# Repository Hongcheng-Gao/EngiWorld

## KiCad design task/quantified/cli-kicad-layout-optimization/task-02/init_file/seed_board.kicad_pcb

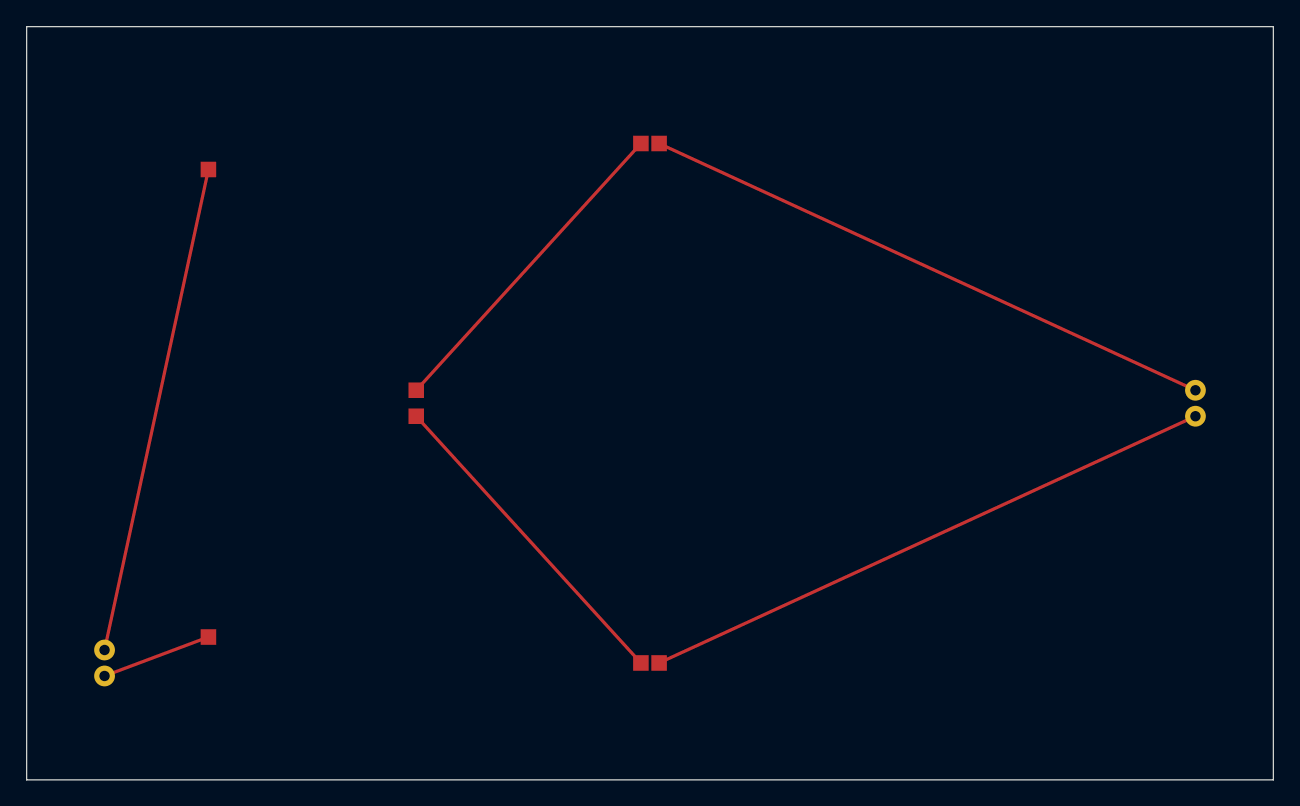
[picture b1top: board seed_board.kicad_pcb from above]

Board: 2 copper layers, 96.0 x 58.0 mm, 7 parts (0 on the bottom side), 6 nets.

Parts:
C1, C2: 100nF
J1: DIFF_CONNECTOR
J2: BYPASS_CONNECTOR
R1, R2: 49.9R
U1: DIFF_DRIVER

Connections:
J2_C1: C1.1, J2.1
J2_C2: C2.1, J2.2
R1_J1: J1.1, R1.2
R2_J1: J1.2, R2.2
U1_R1: R1.1, U1.1
U1_R2: R2.1, U1.2

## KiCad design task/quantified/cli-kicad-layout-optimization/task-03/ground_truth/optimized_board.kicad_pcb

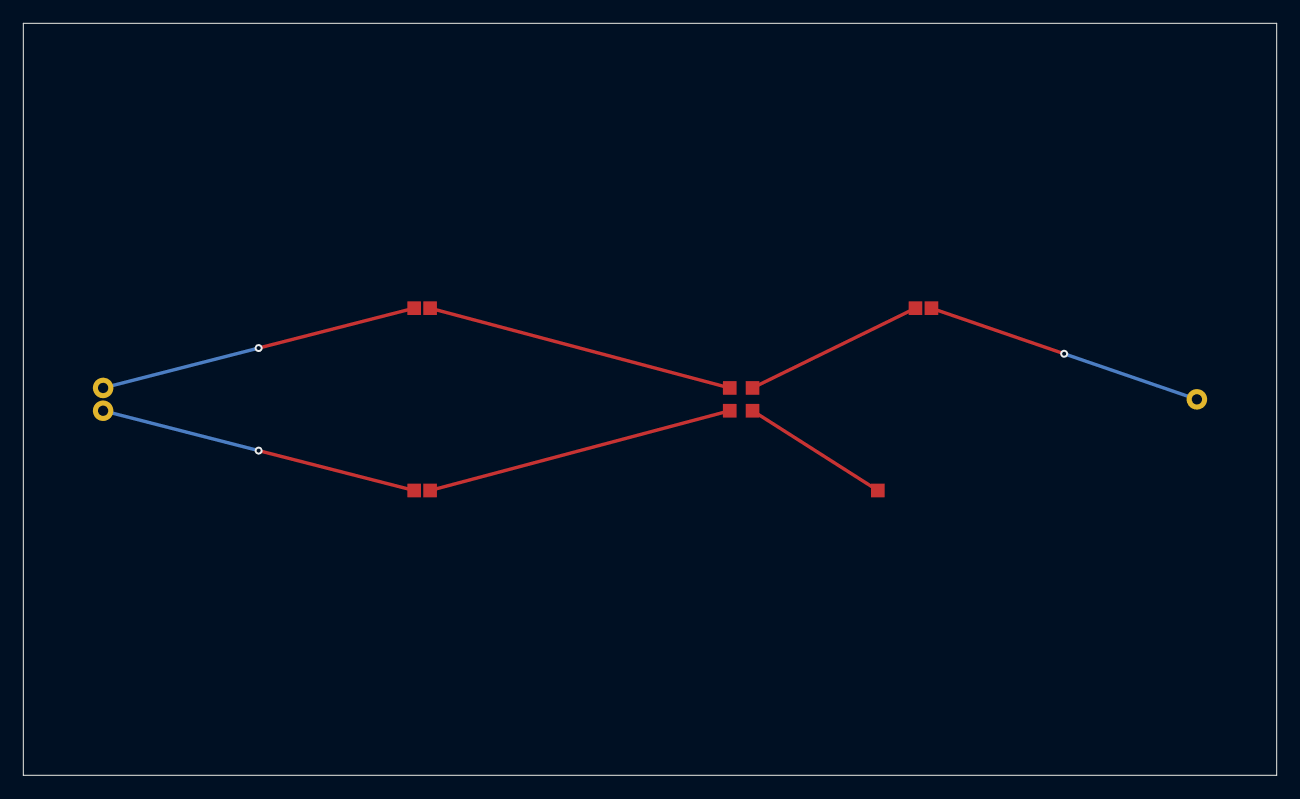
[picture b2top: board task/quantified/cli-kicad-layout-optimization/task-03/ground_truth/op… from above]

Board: 2 copper layers, 110.0 x 66.0 mm, 7 parts (0 on the bottom side), 7 nets.

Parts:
CIN1, CIN2: 47uF
D1: SCHOTTKY
J1: POWER_IN
J2: POWER_OUT
L1: 22uH
U1: REGULATOR

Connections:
CIN1_U1: CIN1.2, U1.1
CIN2_U1: CIN2.2, U1.2
J1_CIN1: CIN1.1, J1.1
J1_CIN2: CIN2.1, J1.2
L1_J2: J2.1, L1.2
U1_D1: D1.1, U1.3
U1_L1: L1.1, U1.4

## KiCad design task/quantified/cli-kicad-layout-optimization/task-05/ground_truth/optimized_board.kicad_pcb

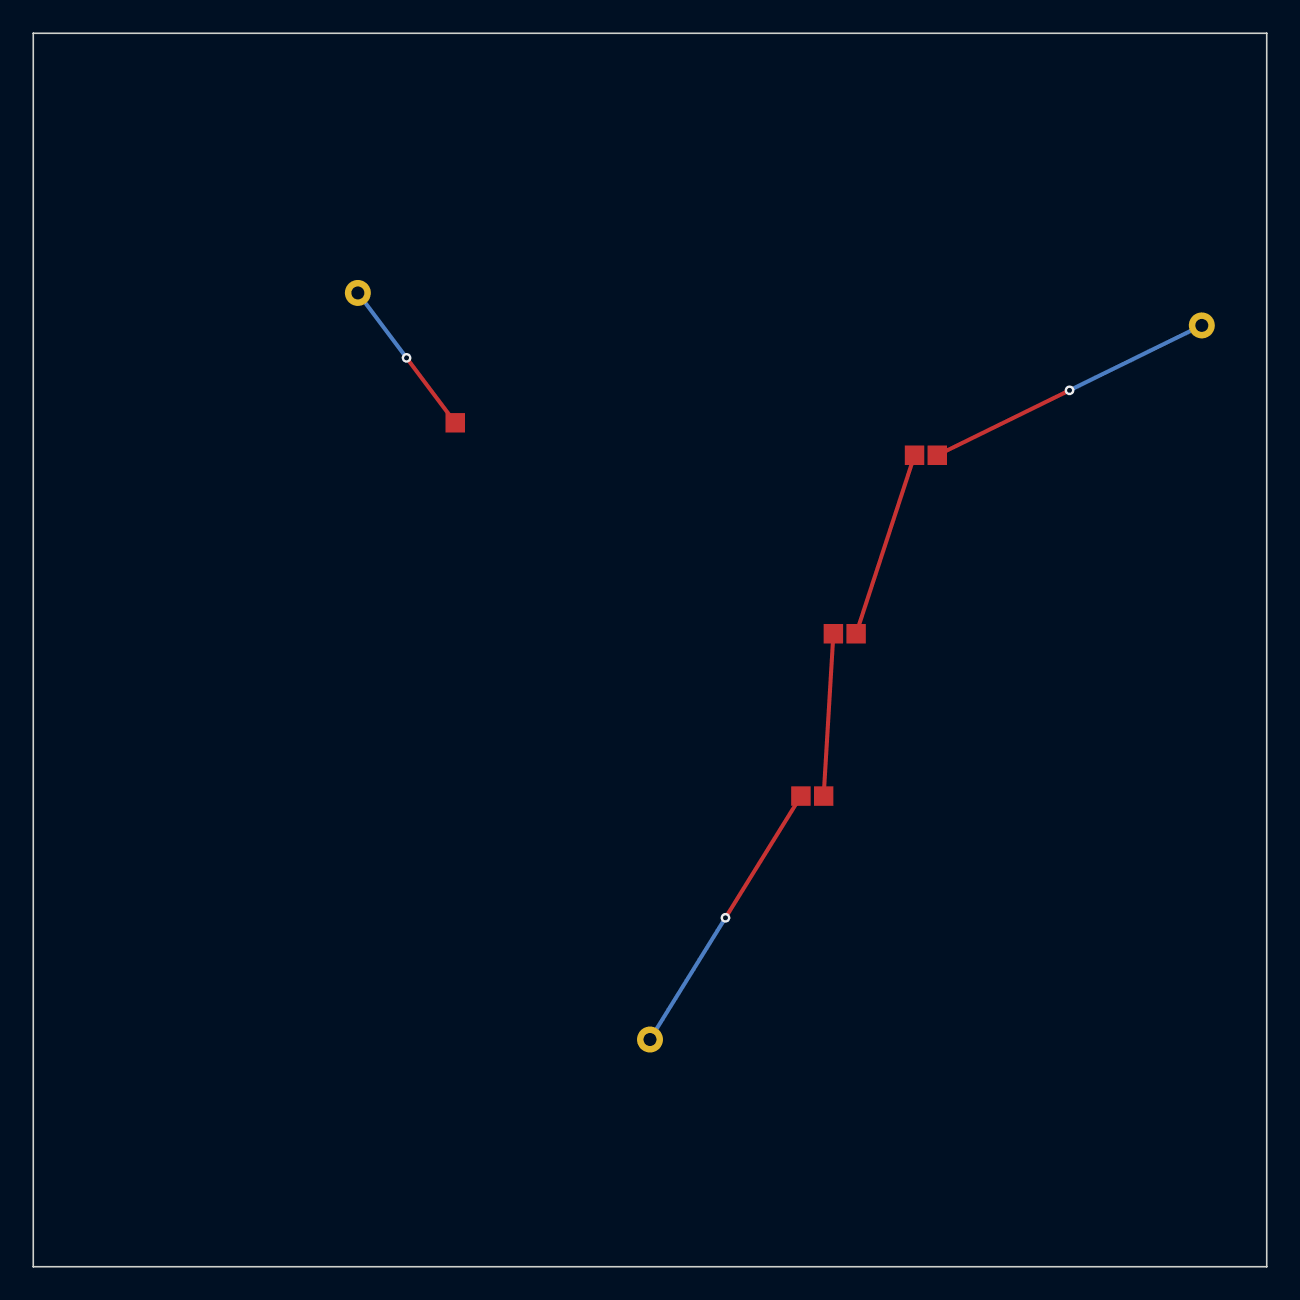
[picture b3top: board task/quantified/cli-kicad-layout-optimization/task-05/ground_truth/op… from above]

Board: 2 copper layers, 76.0 x 76.0 mm, 7 parts (0 on the bottom side), 5 nets.

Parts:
A1: A1
C1: C1
C2: C2
J1: J1
L1: L1
TP1: TP1
U1: U1

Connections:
A1_C1: A1.1, C1.1
C1_C2: C1.2, C2.1
C2_L1: C2.2, L1.1
L1_J1: J1.1, L1.2
U1_TP1: TP1.1, U1.1
